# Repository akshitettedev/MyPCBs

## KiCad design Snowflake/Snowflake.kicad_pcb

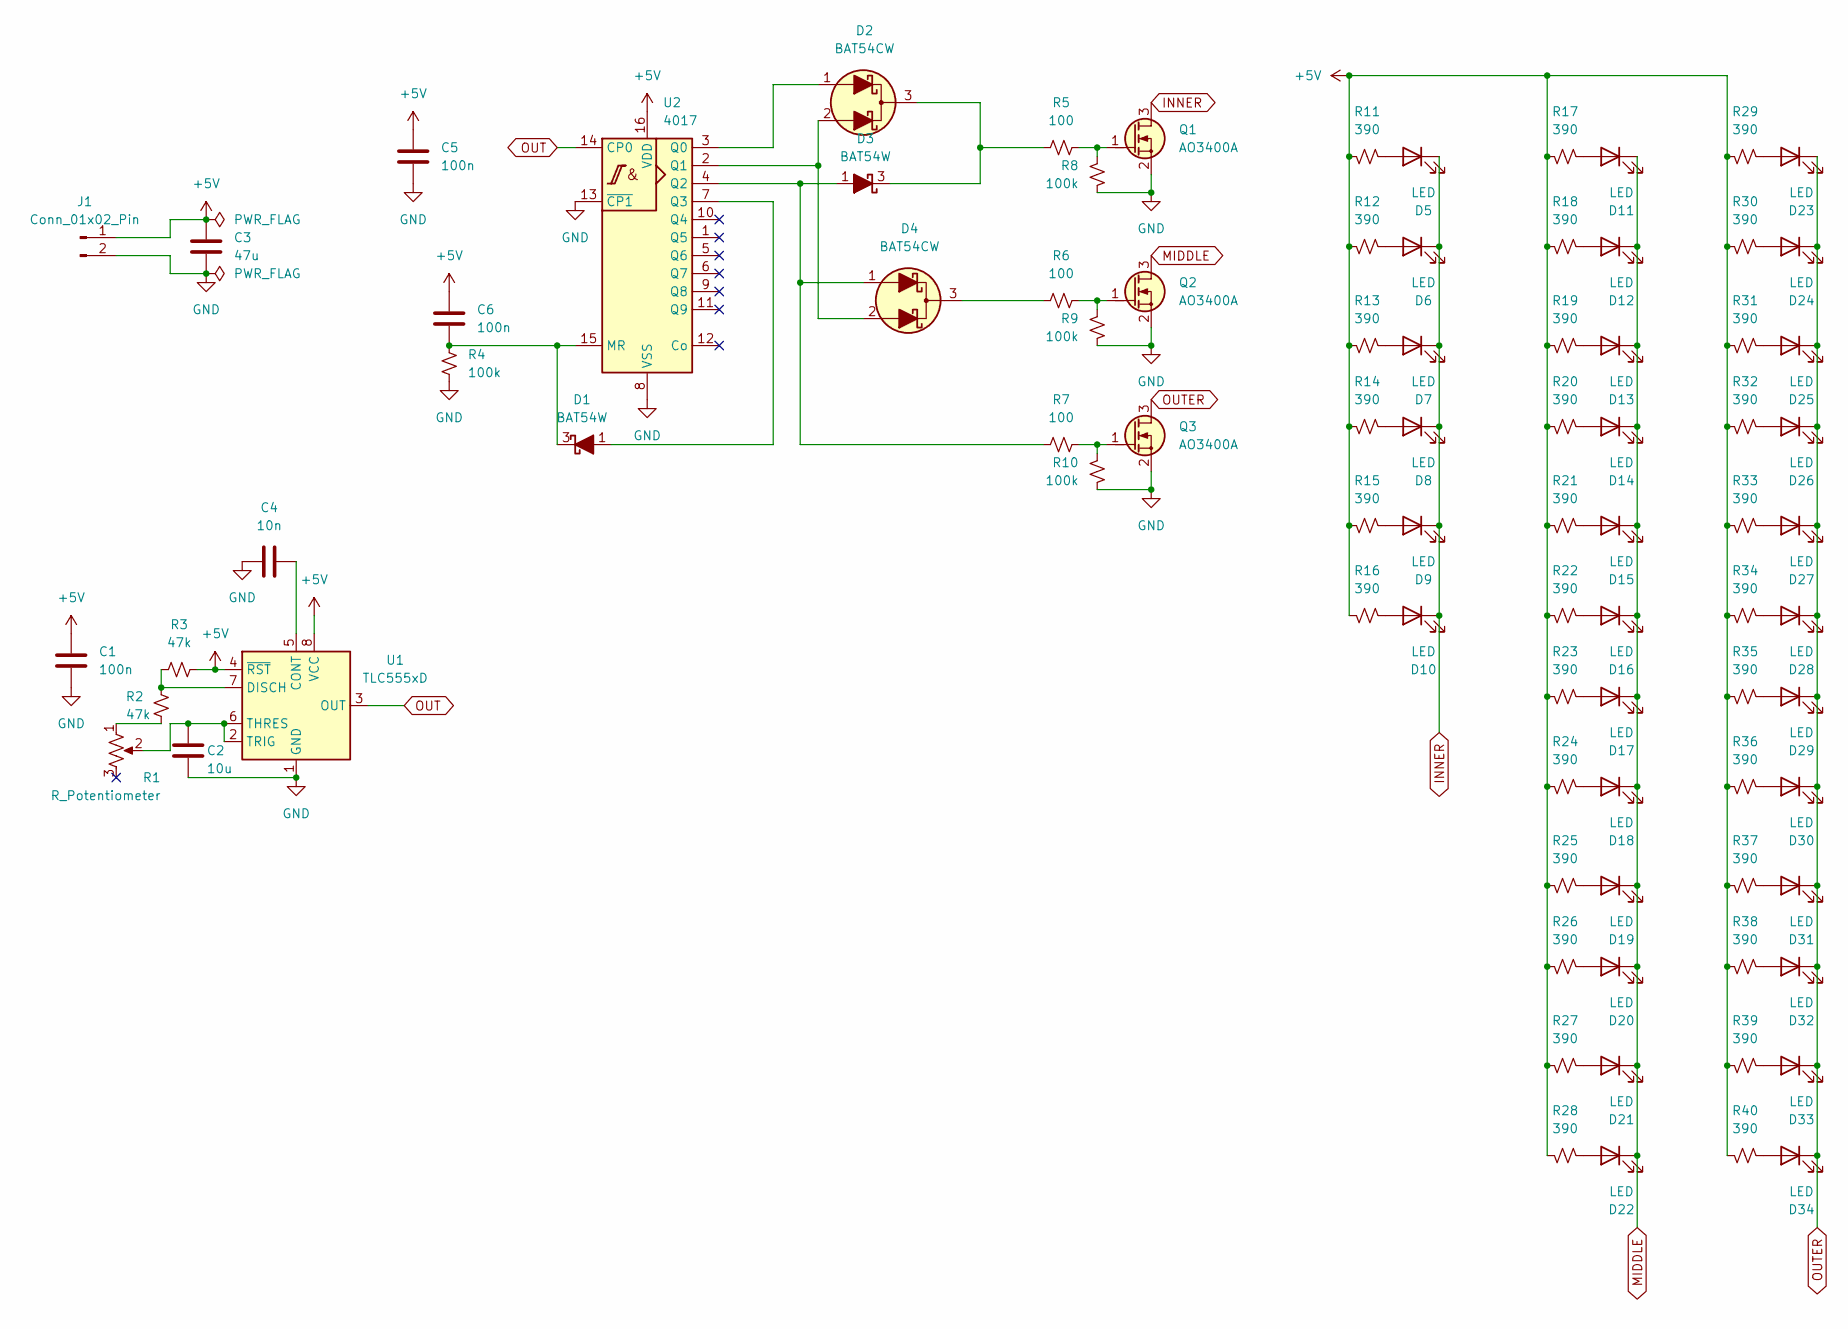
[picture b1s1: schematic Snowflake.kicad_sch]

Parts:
C1, C5, C6: 100n; C_0603_1608Metric_Pad1.08x0.95mm_HandSolder
C2: 10u; C_1206_3216Metric_Pad1.33x1.80mm_HandSolder
C3: 47u; C_1206_3216Metric_Pad1.33x1.80mm_HandSolder
C4: 10n; C_0603_1608Metric_Pad1.08x0.95mm_HandSolder
D1, D3: BAT54W; SOT-323_SC-70
D2, D4: BAT54CW; SOT-323_SC-70
D5, D6, D7, D8, D9, D10, D11, D12, D13, D14, D15, D16, D17, D18, D19, D20, D21, D22, D23, D24, D25, D26, D27, D28, D29, D30, D31, D32, D33, D34: LED; LED_0603_1608Metric_Pad1.05x0.95mm
J1: Conn_01x02_Pin; PinHeader_1x02_P2.54mm_Vertical
Q1, Q2, Q3: AO3400A; SOT-23
R1: R_Potentiometer; Potentiometer_Bourns_3224W_Vertical
R2, R3: 47k; R_0603_1608Metric_Pad1.05x0.95mm_HandSolder
R4, R8, R9, R10: 100k; R_0603_1608Metric_Pad1.05x0.95mm_HandSolder
R5, R6, R7: 100; R_0603_1608Metric_Pad1.05x0.95mm_HandSolder
R11, R12, R13, R14, R15, R16, R17, R18, R19, R20, R21, R22, R23, R24, R25, R26, R27, R28, R29, R30, R31, R32, R33, R34, R35, R36, R37, R38, R39, R40: 390; R_0603_1608Metric_Pad1.05x0.95mm_HandSolder
U1: TLC555xD; SOIC-8_3.9x4.9mm_P1.27mm
U2: 4017; TSSOP-16_4.4x5mm_P0.65mm

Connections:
+5V: C1.1, C3.1, C5.1, C6.1, J1.1, R3.2, R11.2, R12.2, R13.2, R14.2, R15.2, R16.2, R17.2, R18.2, R19.2, R20.2, R21.2, R22.2, R23.2, R24.2, R25.2, R26.2, R27.2, R28.2, R29.2, R30.2, R31.2, R32.2, R33.2, R34.2, R35.2, R36.2, R37.2, R38.2, R39.2, R40.2, U1.4 (~RST), U1.8 (VCC), U2.16 (VDD)
GND: C1.2, C2.2, C3.2, C4.1, C5.2, J1.2, Q1.2 (S), Q2.2 (S), Q3.2 (S), R4.1, R8.1, R9.1, R10.1, U1.1 (GND), U2.8 (VSS), U2.13 (~CP1)
INNER: D5.1 (K), D6.1 (K), D7.1 (K), D8.1 (K), D9.1 (K), D10.1 (K), Q1.3 (D)
MIDDLE: D11.1 (K), D12.1 (K), D13.1 (K), D14.1 (K), D15.1 (K), D16.1 (K), D17.1 (K), D18.1 (K), D19.1 (K), D20.1 (K), D21.1 (K), D22.1 (K), Q2.3 (D)
unnamed: D1.1 (A), U2.7 (Q3)
unnamed: C6.2, D1.3 (K), R4.2, U2.15 (MR)
unnamed: D2.2 (A1), D4.2 (A1), U2.2 (Q1)
unnamed: D2.1 (A2), U2.3 (Q0)
unnamed: D2.3 (K), D3.3 (K), R5.2
unnamed: D3.1 (A), D4.1 (A2), R7.1, U2.4 (Q2)
unnamed: D4.3 (K), R6.1
unnamed: D5.2 (A), R11.1
unnamed: D6.2 (A), R12.1
unnamed: D7.2 (A), R13.1
unnamed: D8.2 (A), R14.1
unnamed: D9.2 (A), R15.1
unnamed: D10.2 (A), R16.1
unnamed: D11.2 (A), R17.1
unnamed: D12.2 (A), R18.1
unnamed: D13.2 (A), R19.1
unnamed: D14.2 (A), R20.1
unnamed: D15.2 (A), R21.1
unnamed: D16.2 (A), R22.1
unnamed: D17.2 (A), R23.1
unnamed: D18.2 (A), R24.1
unnamed: D19.2 (A), R25.1
unnamed: D20.2 (A), R26.1
unnamed: D21.2 (A), R27.1
unnamed: D22.2 (A), R28.1
unnamed: D23.2 (A), R29.1
unnamed: D24.2 (A), R30.1
unnamed: D25.2 (A), R31.1
unnamed: D26.2 (A), R32.1
unnamed: D27.2 (A), R33.1
unnamed: D28.2 (A), R34.1
unnamed: D29.2 (A), R35.1
unnamed: D30.2 (A), R36.1
unnamed: D31.2 (A), R37.1
unnamed: D32.2 (A), R38.1
unnamed: D33.2 (A), R39.1
unnamed: D34.2 (A), R40.1
unnamed: Q1.1 (G), R5.1, R8.2
unnamed: Q2.1 (G), R6.2, R9.2
unnamed: Q3.1 (G), R7.2, R10.2
unnamed: R1.1, R2.1
unnamed: C4.2, U1.5 (CONT)
unnamed: R2.2, R3.1, U1.7 (DISCH)
unnamed: C2.1, R1.2, U1.2 (TRIG), U1.6 (THRES)
OUT: U1.3 (OUT), U2.14 (CP0)
OUTER: D23.1 (K), D24.1 (K), D25.1 (K), D26.1 (K), D27.1 (K), D28.1 (K), D29.1 (K), D30.1 (K), D31.1 (K), D32.1 (K), D33.1 (K), D34.1 (K), Q3.3 (D)

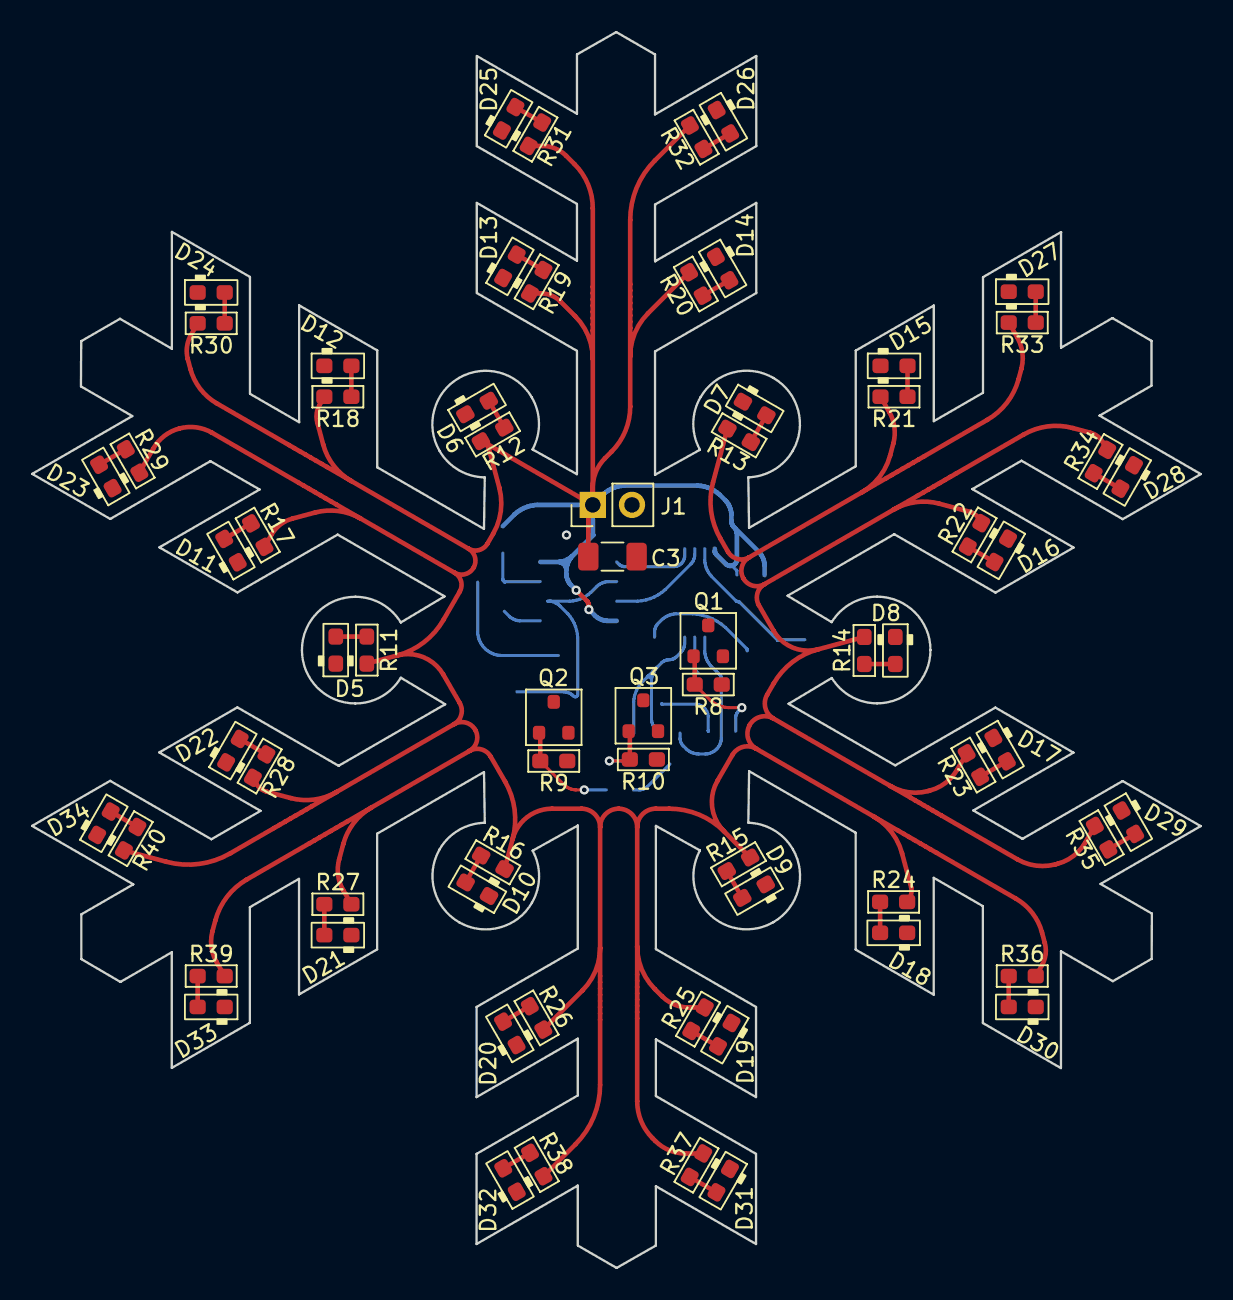
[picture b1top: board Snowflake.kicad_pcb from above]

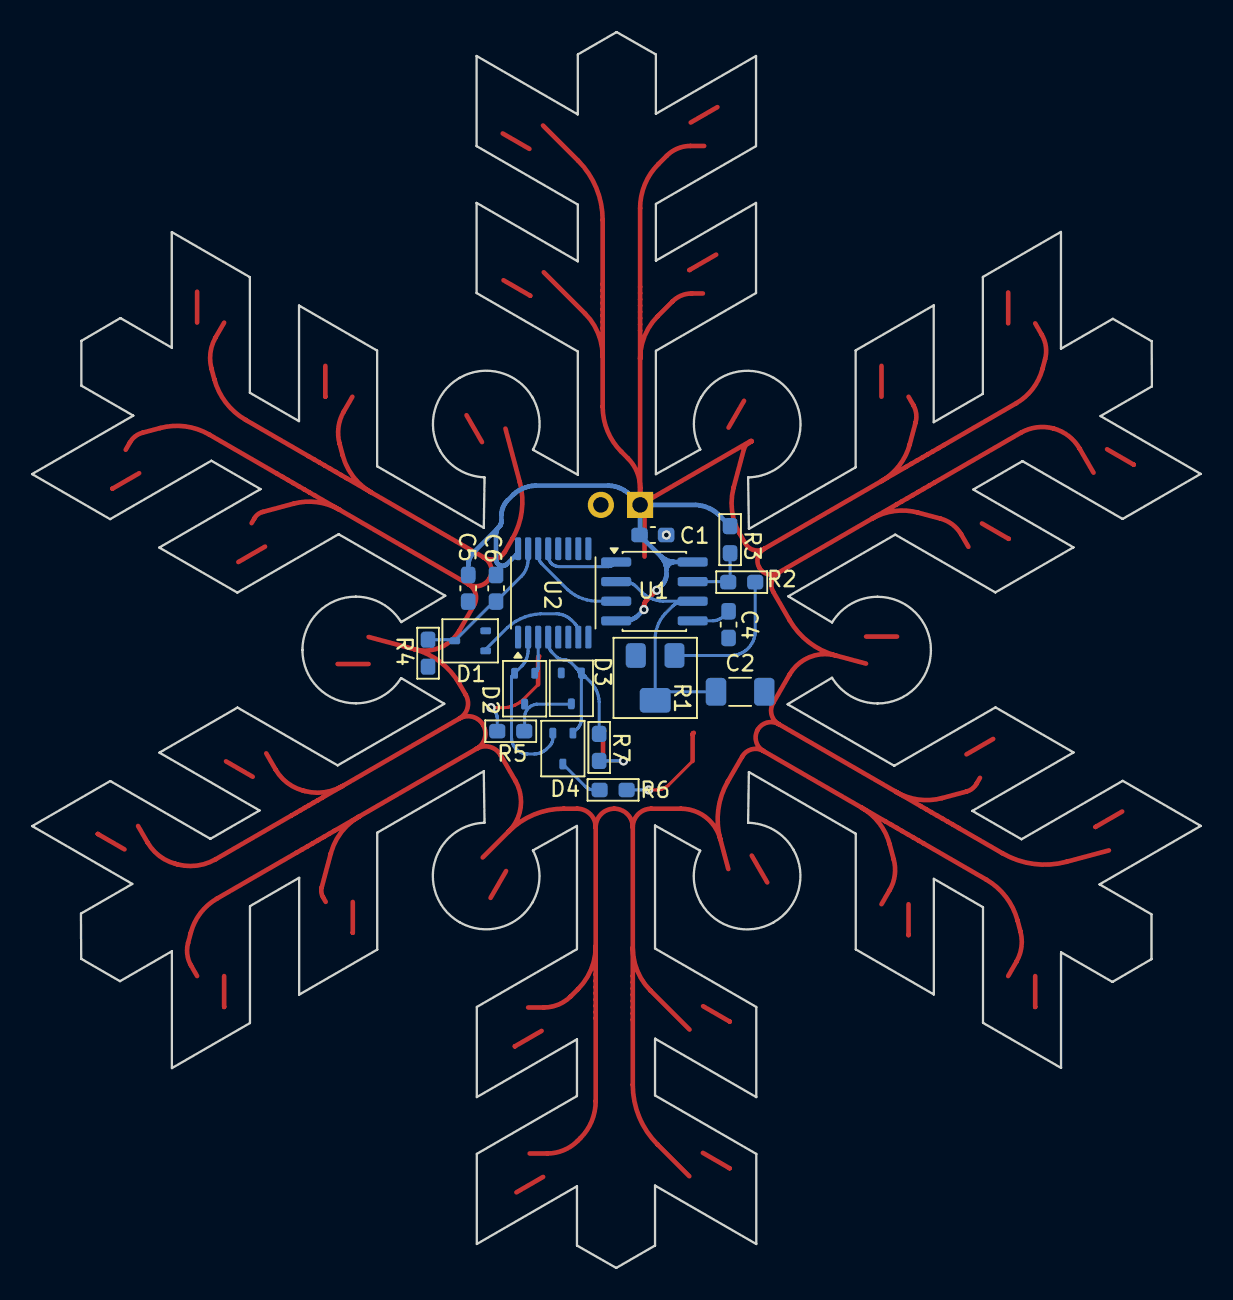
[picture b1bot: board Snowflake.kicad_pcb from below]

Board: 2 copper layers, 75.7 x 80.0 mm, 86 parts (18 on the bottom side), 50 nets.

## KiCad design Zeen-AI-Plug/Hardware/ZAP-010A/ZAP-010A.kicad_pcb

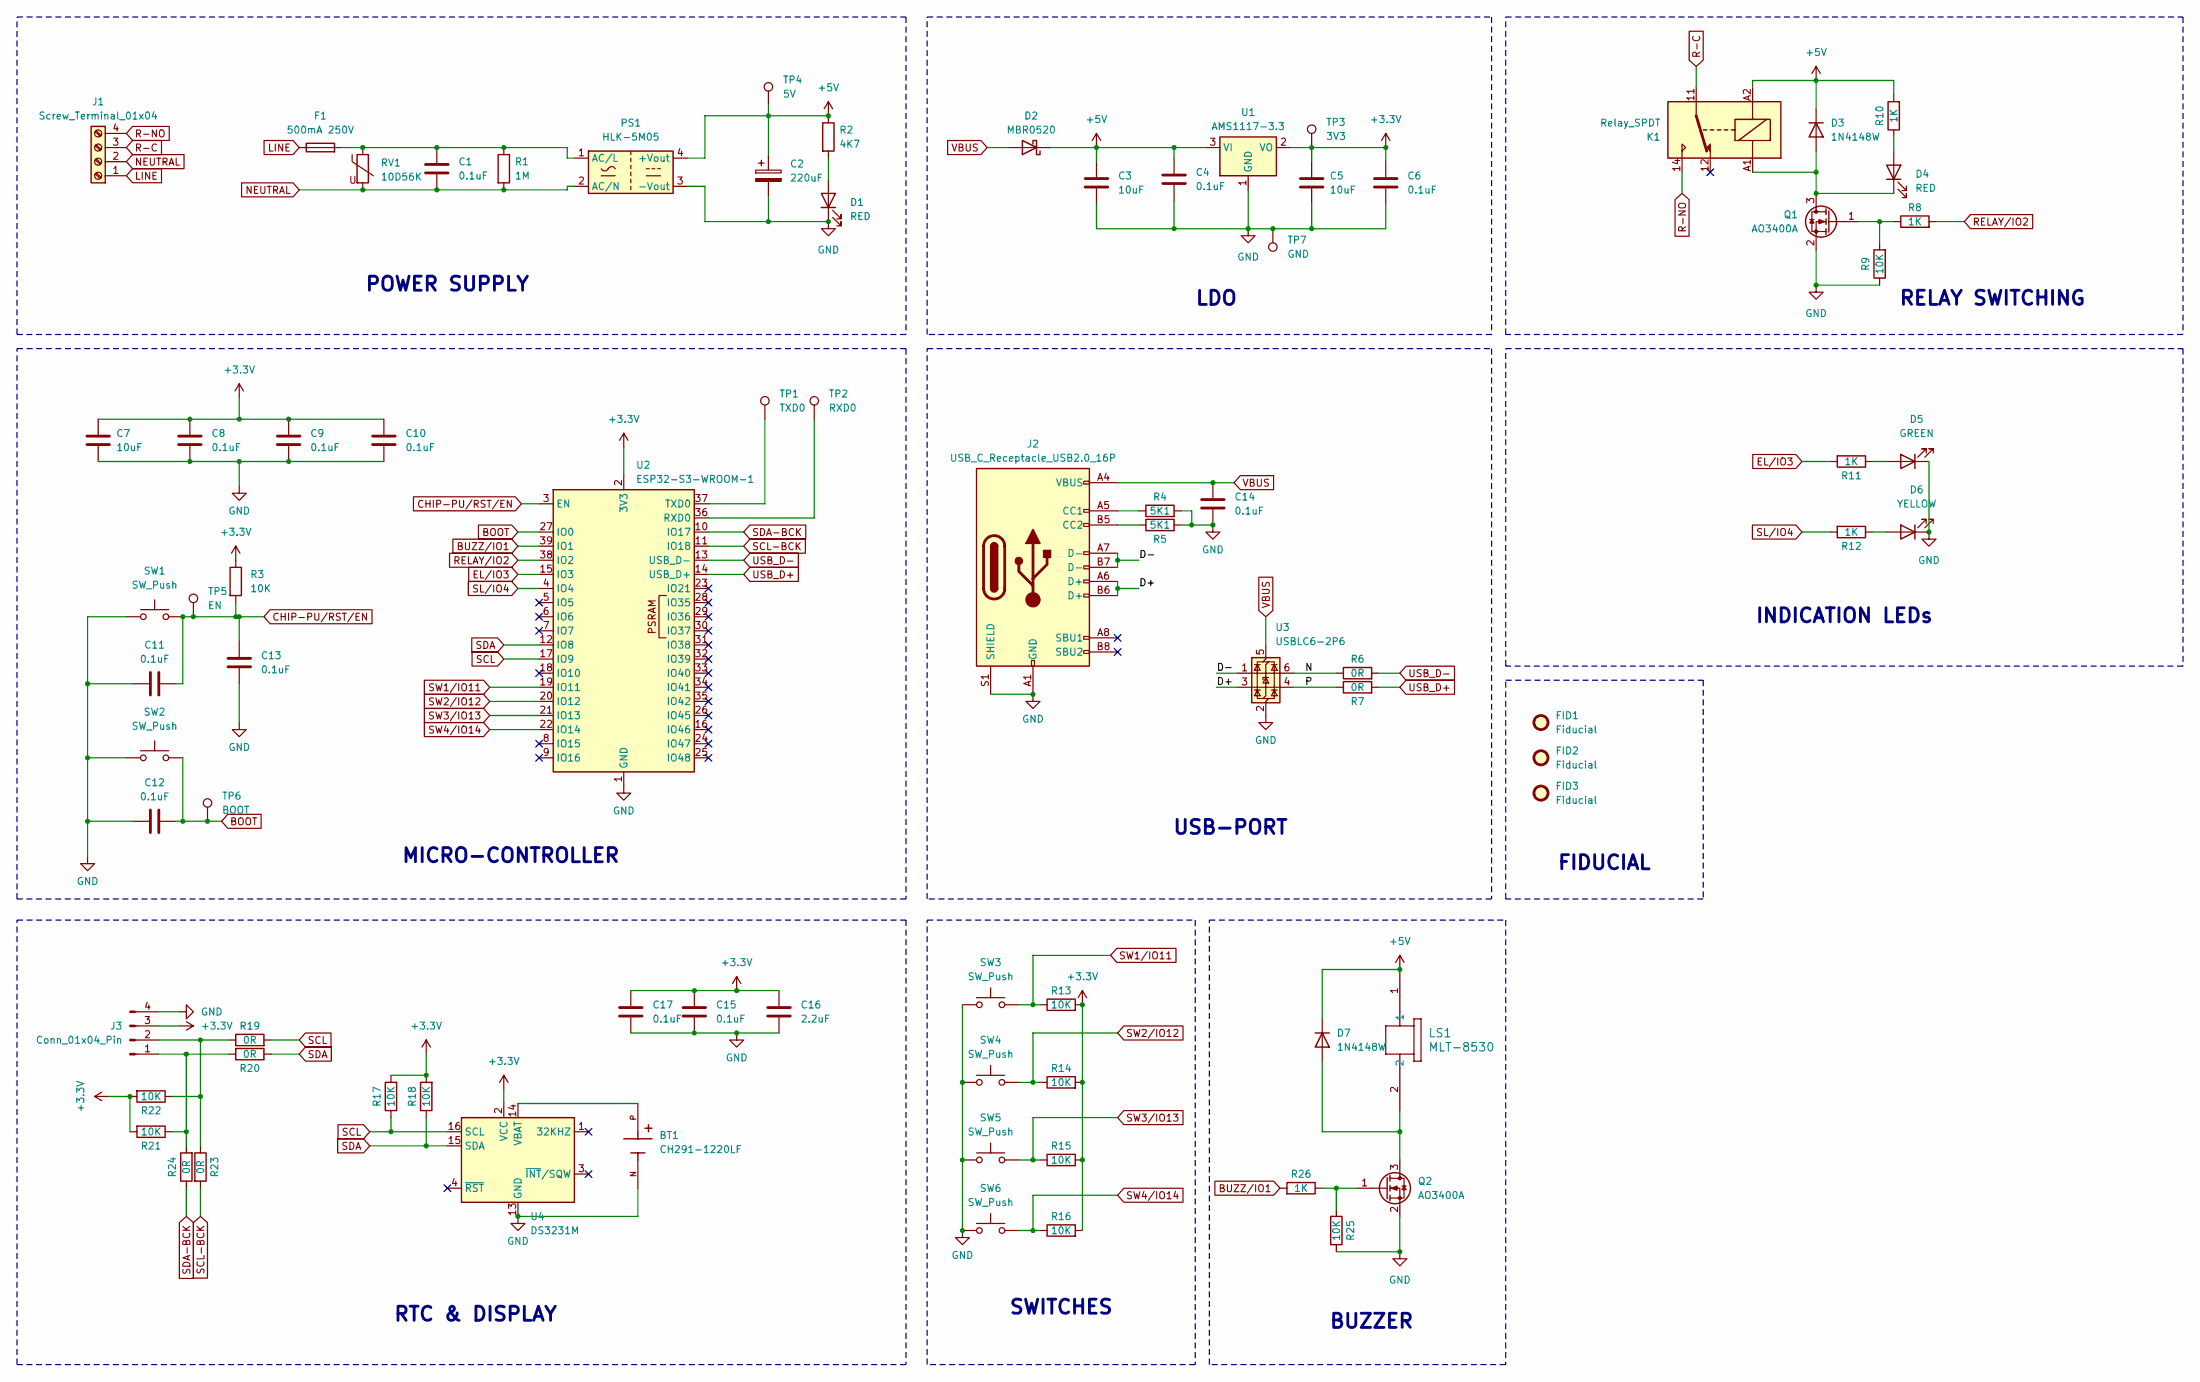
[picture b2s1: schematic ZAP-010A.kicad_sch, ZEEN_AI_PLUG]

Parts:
BT1: CH291-1220LF; BAT_CH291-1220LF; PARTREV A
C1: 0.1uF; C_Rect_L13.0mm_W6.0mm_P10.00mm_FKS3_FKP3_MKS4
C2: 220uF; CP_Elec_8x10
C3, C5, C7: 10uF; C_0805_2012Metric
C4, C6, C8, C9, C10, C11, C12, C13, C14, C15, C17: 0.1uF; C_0603_1608Metric
C16: 2.2uF; C_0805_2012Metric
D1: RED; LED_D3.0mm
D2: MBR0520; D_SOD-123
D3, D7: 1N4148W; D_SOD-123
D4: RED; LED_0603_1608Metric
D5: GREEN; LED_D3.0mm
D6: YELLOW; LED_D3.0mm
F1: 500mA 250V; Fuse_Littelfuse_395Series
FID1, FID2, FID3: Fiducial; Fiducial_0.75mm_Mask1.5mm
J1: Screw_Terminal_01x04; TerminalBlock_CUI_TB007-508-04_1x04_P5.08mm_Horizontal
J2: USB_C_Receptacle_USB2.0_16P; USB_C_Receptacle_HCTL_HC-TYPE-C-16P-01A
J3: Conn_01x04_Pin; PinHeader_1x04_P2.54mm_Vertical
K1: Relay_SPDT; Relay_SPDT_Hongfa_HF3F-L-xx-1ZL1T
LS1: MLT-8530; MLT-8530_JHE
PS1: HLK-5M05; Converter_ACDC_Hi-Link_HLK-5Mxx
Q1, Q2: AO3400A; SOT-23
R1: 1M; R_Axial_DIN0207_L6.3mm_D2.5mm_P7.62mm_Horizontal
R2: 4K7; R_0603_1608Metric
R3, R9, R13, R14, R15, R16, R17, R18, R21, R22, R25: 10K; R_0603_1608Metric
R4, R5: 5K1; R_0603_1608Metric
R6, R7, R19, R20, R23, R24: 0R; R_0603_1608Metric
R8, R10, R11, R12, R26: 1K; R_0603_1608Metric
RV1: 10D56K; RV_Disc_D12mm_W5.8mm_P7.5mm
SW1, SW3, SW4, SW5, SW6: SW_Push; SW_PUSH_6mm
SW2: SW_Push; SW_Push_SPST_NO_Alps_SKRK
TP1: TXD0; TestPoint_Pad_D1.5mm
TP2: RXD0; TestPoint_Pad_D1.5mm
TP3: 3V3; TestPoint_Pad_D1.5mm
TP4: 5V; TestPoint_Pad_D1.5mm
TP5: EN; TestPoint_Pad_D1.5mm
TP6: BOOT; TestPoint_Pad_D1.5mm
TP7: GND; TestPoint_Pad_D1.5mm
U1: AMS1117-3.3; SOT-223-3_TabPin2
U2: ESP32-S3-WROOM-1
U3: USBLC6-2P6; SOT-666
U4: DS3231M; SOIC-16W_7.5x10.3mm_P1.27mm

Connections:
+3.3V: C5.1, C6.1, C7.1, C8.1, C9.1, C10.1, C15.2, C16.2, C17.2, J3.3, R3.1, R13.2, R14.2, R15.2, R16.2, R17.2, R18.2, R21.2, R22.2, TP3.1, U1.2 (VO), U2.2 (3V3), U4.2 (VCC)
+5V: C2.1, C3.1, C4.1, D2.1 (K), D3.1 (K), D7.1 (K), K1.A2, LS1.1, PS1.4 (+Vout), R2.1, R10.2, TP4.1, U1.3 (VI)
/D+: J2.A6 (D+), J2.B6 (D+), U3.3 (I/O2)
/D-: J2.A7 (D-), J2.B7 (D-), U3.1 (I/O1)
/N: R6.1, U3.6 (I/O1)
/P: R7.1, U3.4 (I/O2)
BOOT: C12.2, SW2.2, TP6.1, U2.27 (IO0)
BUZZ/IO1: R26.2, U2.39 (IO1)
CHIP-PU/RST/EN: C11.2, C13.2, R3.2, SW1.2, TP5.1, U2.3 (EN)
EL/IO3: R11.2, U2.15 (IO3)
GND: BT1.N, C2.2, C3.2, C4.2, C5.2, C6.2, C7.2, C8.2, C9.2, C10.2, C11.1, C12.1, C13.1, C14.2, C15.1, C16.1, C17.1, D1.1 (K), D5.1 (K), D6.1 (K), J2.A1 (GND), J2.A12 (GND), J2.B1 (GND), J2.B12 (GND), J2.S1 (SHIELD), J3.4, PS1.3 (-Vout), Q1.2 (S), Q2.2 (S), R4.2, R5.2, R9.1, R25.1, SW1.1, SW2.1, SW3.1, SW4.1, SW5.1, SW6.1, TP7.1, U1.1 (GND), U2.1 (GND), U2.40 (GND), U2.41 (GND), U3.2 (GND), U4.5 (GND), U4.6 (GND), U4.7 (GND), U4.8 (GND), U4.9 (GND), U4.10 (GND), U4.11 (GND), U4.12 (GND), U4.13 (GND)
LINE: F1.1, J1.1
NEUTRAL: C1.2, J1.2, PS1.2 (AC/N), R1.2, RV1.2
unnamed: D1.2 (A), R2.2
unnamed: D3.2 (A), D4.1 (K), K1.A1, Q1.3 (D)
unnamed: D4.2 (A), R10.1
unnamed: D5.2 (A), R11.1
unnamed: D6.2 (A), R12.1
unnamed: D7.2 (A), LS1.2, Q2.3 (D)
unnamed: J2.A5 (CC1), R4.1
unnamed: J2.B5 (CC2), R5.1
unnamed: J3.1, R20.2, R21.1, R24.2
unnamed: J3.2, R19.1, R22.1, R23.1
unnamed: C1.1, F1.2, PS1.1 (AC/L), R1.1, RV1.1
unnamed: Q1.1 (G), R8.1, R9.2
unnamed: Q2.1 (G), R25.2, R26.1
unnamed: TP2.1, U2.36 (RXD0)
unnamed: TP1.1, U2.37 (TXD0)
unnamed: BT1.P, U4.14 (VBAT)
R-C: J1.3, K1.11
R-NO: J1.4, K1.14
RELAY/IO2: R8.2, U2.38 (IO2)
SCL: R17.1, R19.2, U2.17 (IO9), U4.16 (SCL)
SCL-BCK: R23.2, U2.11 (IO18)
SDA: R18.1, R20.1, U2.12 (IO8), U4.15 (SDA)
SDA-BCK: R24.1, U2.10 (IO17)
SL/IO4: R12.2, U2.4 (IO4)
SW1/IO11: R13.1, SW3.2, U2.19 (IO11)
SW2/IO12: R14.1, SW4.2, U2.20 (IO12)
SW3/IO13: R15.1, SW5.2, U2.21 (IO13)
SW4/IO14: R16.1, SW6.2, U2.22 (IO14)
USB_D+: R7.2, U2.14 (USB_D+)
USB_D-: R6.2, U2.13 (USB_D-)
VBUS: C14.1, D2.2 (A), J2.A4 (VBUS), J2.A9 (VBUS), J2.B4 (VBUS), J2.B9 (VBUS), U3.5 (VBUS)

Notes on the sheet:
SWITCHES
LDO
FIDUCIAL
MICRO-CONTROLLER
BUZZER
RELAY SWITCHING
RTC & DISPLAY
POWER SUPPLY
USB-PORT
INDICATION LEDs

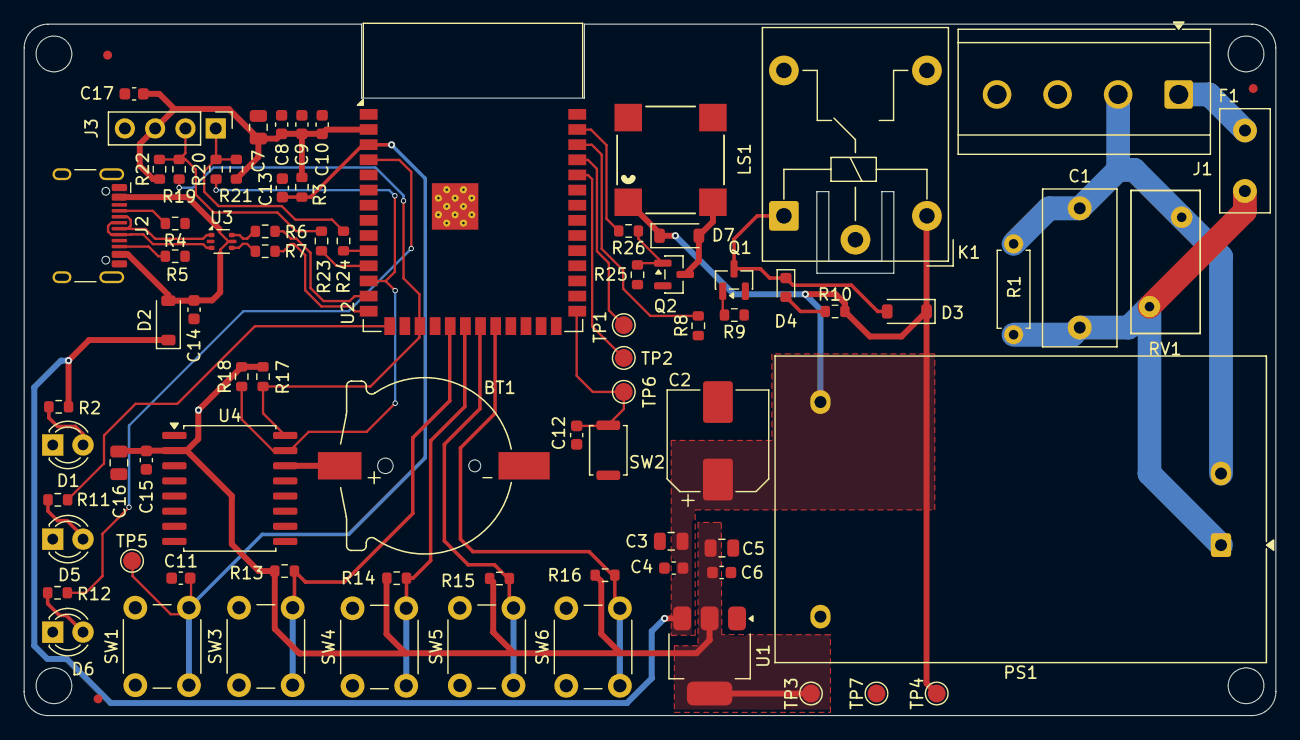
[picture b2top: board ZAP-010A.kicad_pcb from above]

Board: 2 copper layers, 105.0 x 58.0 mm, 81 parts (0 on the bottom side), 44 nets.

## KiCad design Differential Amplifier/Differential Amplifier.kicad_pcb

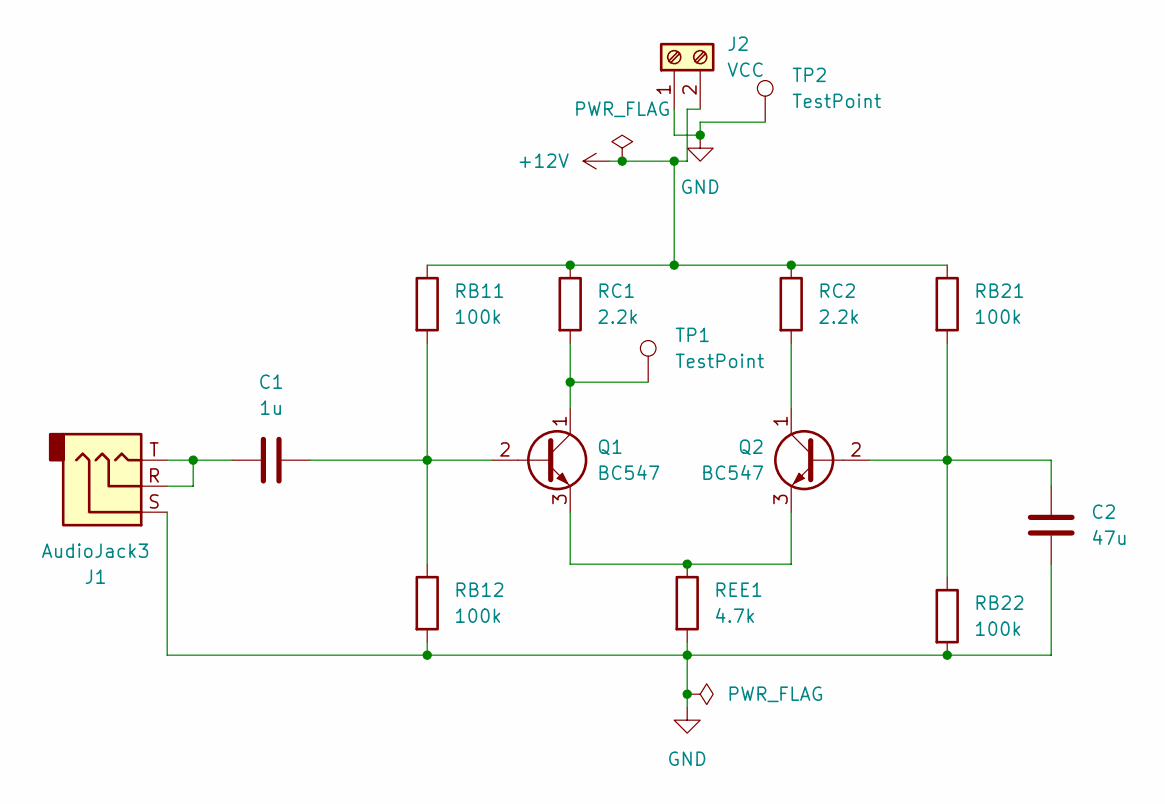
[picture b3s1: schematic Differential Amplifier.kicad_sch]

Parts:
C1: 1u; C_Radial_D6.3mm_H5.0mm_P2.50mm
C2: 47u; CP_Radial_D5.0mm_P2.00mm
J1: AudioJack3; Jack_3.5mm_CUI_SJ1-3523N_Horizontal
J2: VCC; TerminalBlock_Phoenix_MKDS-1,5-2-5.08_1x02_P5.08mm_Horizont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
Q1, Q2: BC547; TO-92_Inline
RB11, RB12, RB21, RB22: 100k; R_Axial_DIN0207_L6.3mm_D2.5mm_P7.62mm_Horizontal
RC1, RC2: 2.2k; R_Axial_DIN0207_L6.3mm_D2.5mm_P7.62mm_Horizontal
REE1: 4.7k; R_Axial_DIN0207_L6.3mm_D2.5mm_P7.62mm_Horizontal
TP1, TP2: TestPoint; TestPoint_Loop_D1.80mm_Drill1.0mm_Beaded

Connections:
+12V: J2.2, RB11.1, RB21.1, RC1.1, RC2.1
GND: C2.2, J1.S, J2.1, RB12.2, RB22.2, REE1.2, TP2.1
unnamed: C1.1, J1.R, J1.T
unnamed: C1.2, Q1.2 (B), RB11.2, RB12.1
unnamed: Q1.1 (C), RC1.2, TP1.1
unnamed: Q1.3 (E), Q2.3 (E), REE1.1
unnamed: C2.1, Q2.2 (B), RB21.2, RB22.1
unnamed: Q2.1 (C), RC2.2

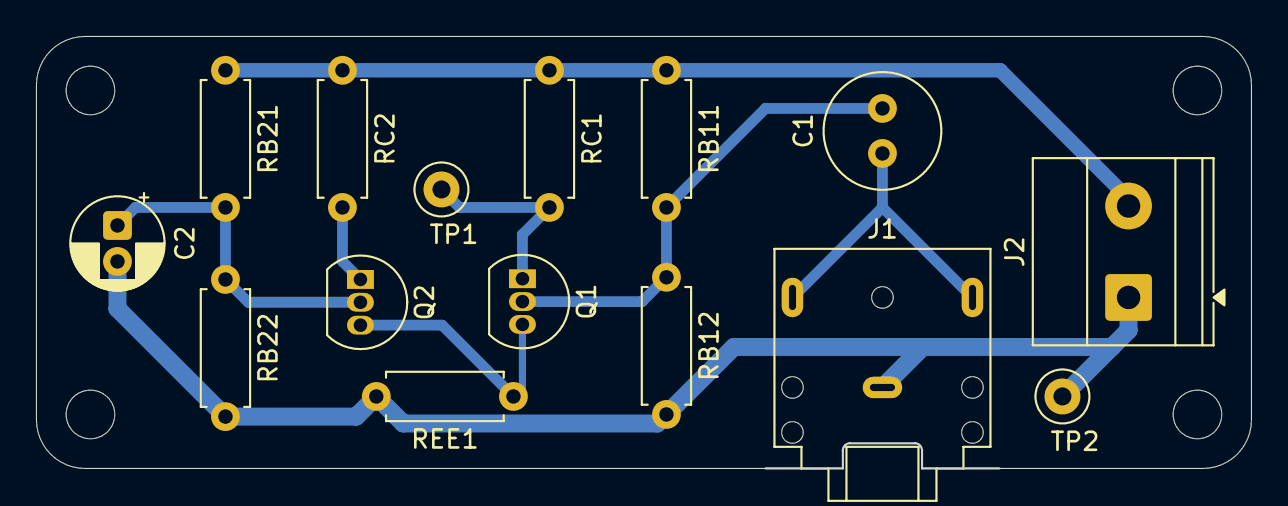
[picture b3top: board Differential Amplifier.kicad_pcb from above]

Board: 2 copper layers, 67.5 x 24.0 mm, 15 parts (0 on the bottom side), 8 nets.
